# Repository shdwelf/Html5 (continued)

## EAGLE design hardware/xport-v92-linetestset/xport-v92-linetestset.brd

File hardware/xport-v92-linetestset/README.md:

# Isolated Line Test Set — `xport-v92-linetestset`

A lineman's test handset on a board. Test leads on one side, an earpiece and an
electret microphone on the other, with a 600:600 Ω wet isolation transformer in
between and a switch that chooses whether you are *part of* the call or merely
listening to it.

This is the legitimate member of the phreaking "box" family — the **beige box**,
which is not a fraud device at all but a standard telecom maintenance tool that
Fluke and Greenlee sell commercially. Clipping it onto a line that is not yours
is wiretapping and is illegal; the hardware is not. See
[`docs/phreaking-boxes-vlsi-notes.md`](../../docs/phreaking-boxes-vlsi-notes.md)
for the rest of that family and why this one is different.

Generated from
[`tools/xport-v92-linetestset-model.mjs`](../../tools/xport-v92-linetestset-model.mjs)
and verified by that tool's `--check`:

```
geometry: 69 pads, 33 placed elements, 27 nets
worst mains↔SELV creepage: 3.28 mm (T1.1 ↔ T1.6), limit 3 mm
schematic: 29 instances on a 520 × 420 mm sheet
OK — XML well-formed, every reference resolves, connectivity matches the model, geometry clean.
```

## Signal chain

```
test leads
  └─ F1 100mA ─ R1/R2 100R ─┬─ RV1 275V ─┬─ C1 100nF ─┐
                            └────────────┴────────────┴─ BR1 bridge rectifier
                                                            └─ K1 hook relay
                                                                 └─ T1 wet 600:600
                                                                      └─ hybrid
                                                                          ├─ TALK 600R ──► earpiece + electret
                                                                          └─ MON  10k ──► volume ──► earpiece
```

## The three things that make it a test set and not an audio tap

**1. The bridge rectifier.** A test set gets clipped onto pairs whose polarity
nobody knows. Full-wave rectifying ahead of everything else means the rest of
the circuit always sees the same orientation. Without `BR1`, half of every job
is guessing which lead is tip.

**2. TALK versus MONITOR are opposite requirements.** TALK goes off-hook and
terminates the line in 600 Ω so you can join the conversation. MONITOR bridges
at 10 kΩ, which is high enough not to load the line or disturb a call already in
progress, so you can listen and measure without anyone knowing. `SW1` selects
between them; there is no setting that does both.

**3. It runs from the line.** The electret bias (`R7` 2.2 k) and the line-present
LED (`R8` 1 k) are fed from the rectified loop. No battery to be flat when you
are standing at a cabinet in the rain, and the LED glows on ring voltage too, so
it doubles as an EMF indicator.

## DC loop budget in TALK

This decides whether the exchange sees an off-hook at all.

| element | resistance |
| --- | --- |
| F1 fuse | ~0.2 Ω |
| R1 + R2 surge limiters | 200 Ω |
| BR1 bridge | a few Ω effective |
| K1 contact | ~0.1 Ω |
| T1 primary DC resistance | 40–150 Ω |
| **total** | **240–350 Ω** (limit 400 Ω) |

## Safety

The left of the board is line-referenced. 48 V DC sits on the pair, ring peaks
above 150 V, and a lightning or power-cross event puts far more on it.

`T1` is the **only** isolation barrier between the line and the earpiece you put
against your head. It must be the **wet** type — specified to carry 20–50 mA of
DC loop current without saturating. A dry voice transformer of the same
impedance works on the bench and fails the moment the line goes off-hook.

Isolation resistance from the line side to any touchable metal has to hold
**5 MΩ measured at 100 V DC**. Measure it after assembly, before first use.

The 3 mm creepage is enforced by `tools/wallplug-drc.mjs` via
`BOARD.zones.mains` and `creepageMm: 3.0`, and `T1`'s primary pins are marked
line-referenced individually through `PARTS[].padZones`, so the checker measures
the transformer's own pin spacing rather than trusting its silk outline. As
built, the worst pair is **T1.1 ↔ T1.6 at 3.28 mm**.

## Files

| file | what |
| --- | --- |
| `xport-v92-linetestset.lbr` | 18 packages, 18 symbols, 19 devicesets |
| `xport-v92-linetestset.sch` | 29 instances on a 520 × 420 sheet |
| `xport-v92-linetestset.brd` | 69 pads, 33 elements, 27 nets, 110 × 80 mm |
| `BOM.md` | generated bill of materials |

Rebuild with `npm run build:xport-v92-linetestset`, or check without writing:
`node tools/build-wallplug-eagle.mjs --check --design xport-v92-linetestset`.

Fourteen of the packages are shared with
[`../xport-v92-audiobridge/`](../xport-v92-audiobridge/) by direct import rather
than by copy, so the two boards cannot drift apart on a footprint. Only the
bridge rectifier, SPDT toggle, earpiece and electret are new.

## What is not done

- **No routing.** The emitter places parts and verifies clearance; it does not
  route copper. `POUR` and the barrier keep-out are declared, traces are not.
- **Not measured.** No prototype. Return loss against the 10 dB requirement,
  frequency response, sidetone null and THD are all unmeasured, and the hybrid
  balance in particular has to be trimmed against a real line.
- **No sidetone or ringer.** A production butt set has both. This has an
  earpiece, a microphone and a volume control, and nothing else.
- **`LS1` and `MIC1` values are placeholders.** A 150 Ω earpiece and a generic
  electret are assumed; the bias resistor `R7`/`R10` divider was sized for a
  typical 2 V, 0.5 mA capsule, not for a specific part.
- **Hook drive is external.** `J2` expects a control signal; the set does not
  decide for itself when to go off-hook.

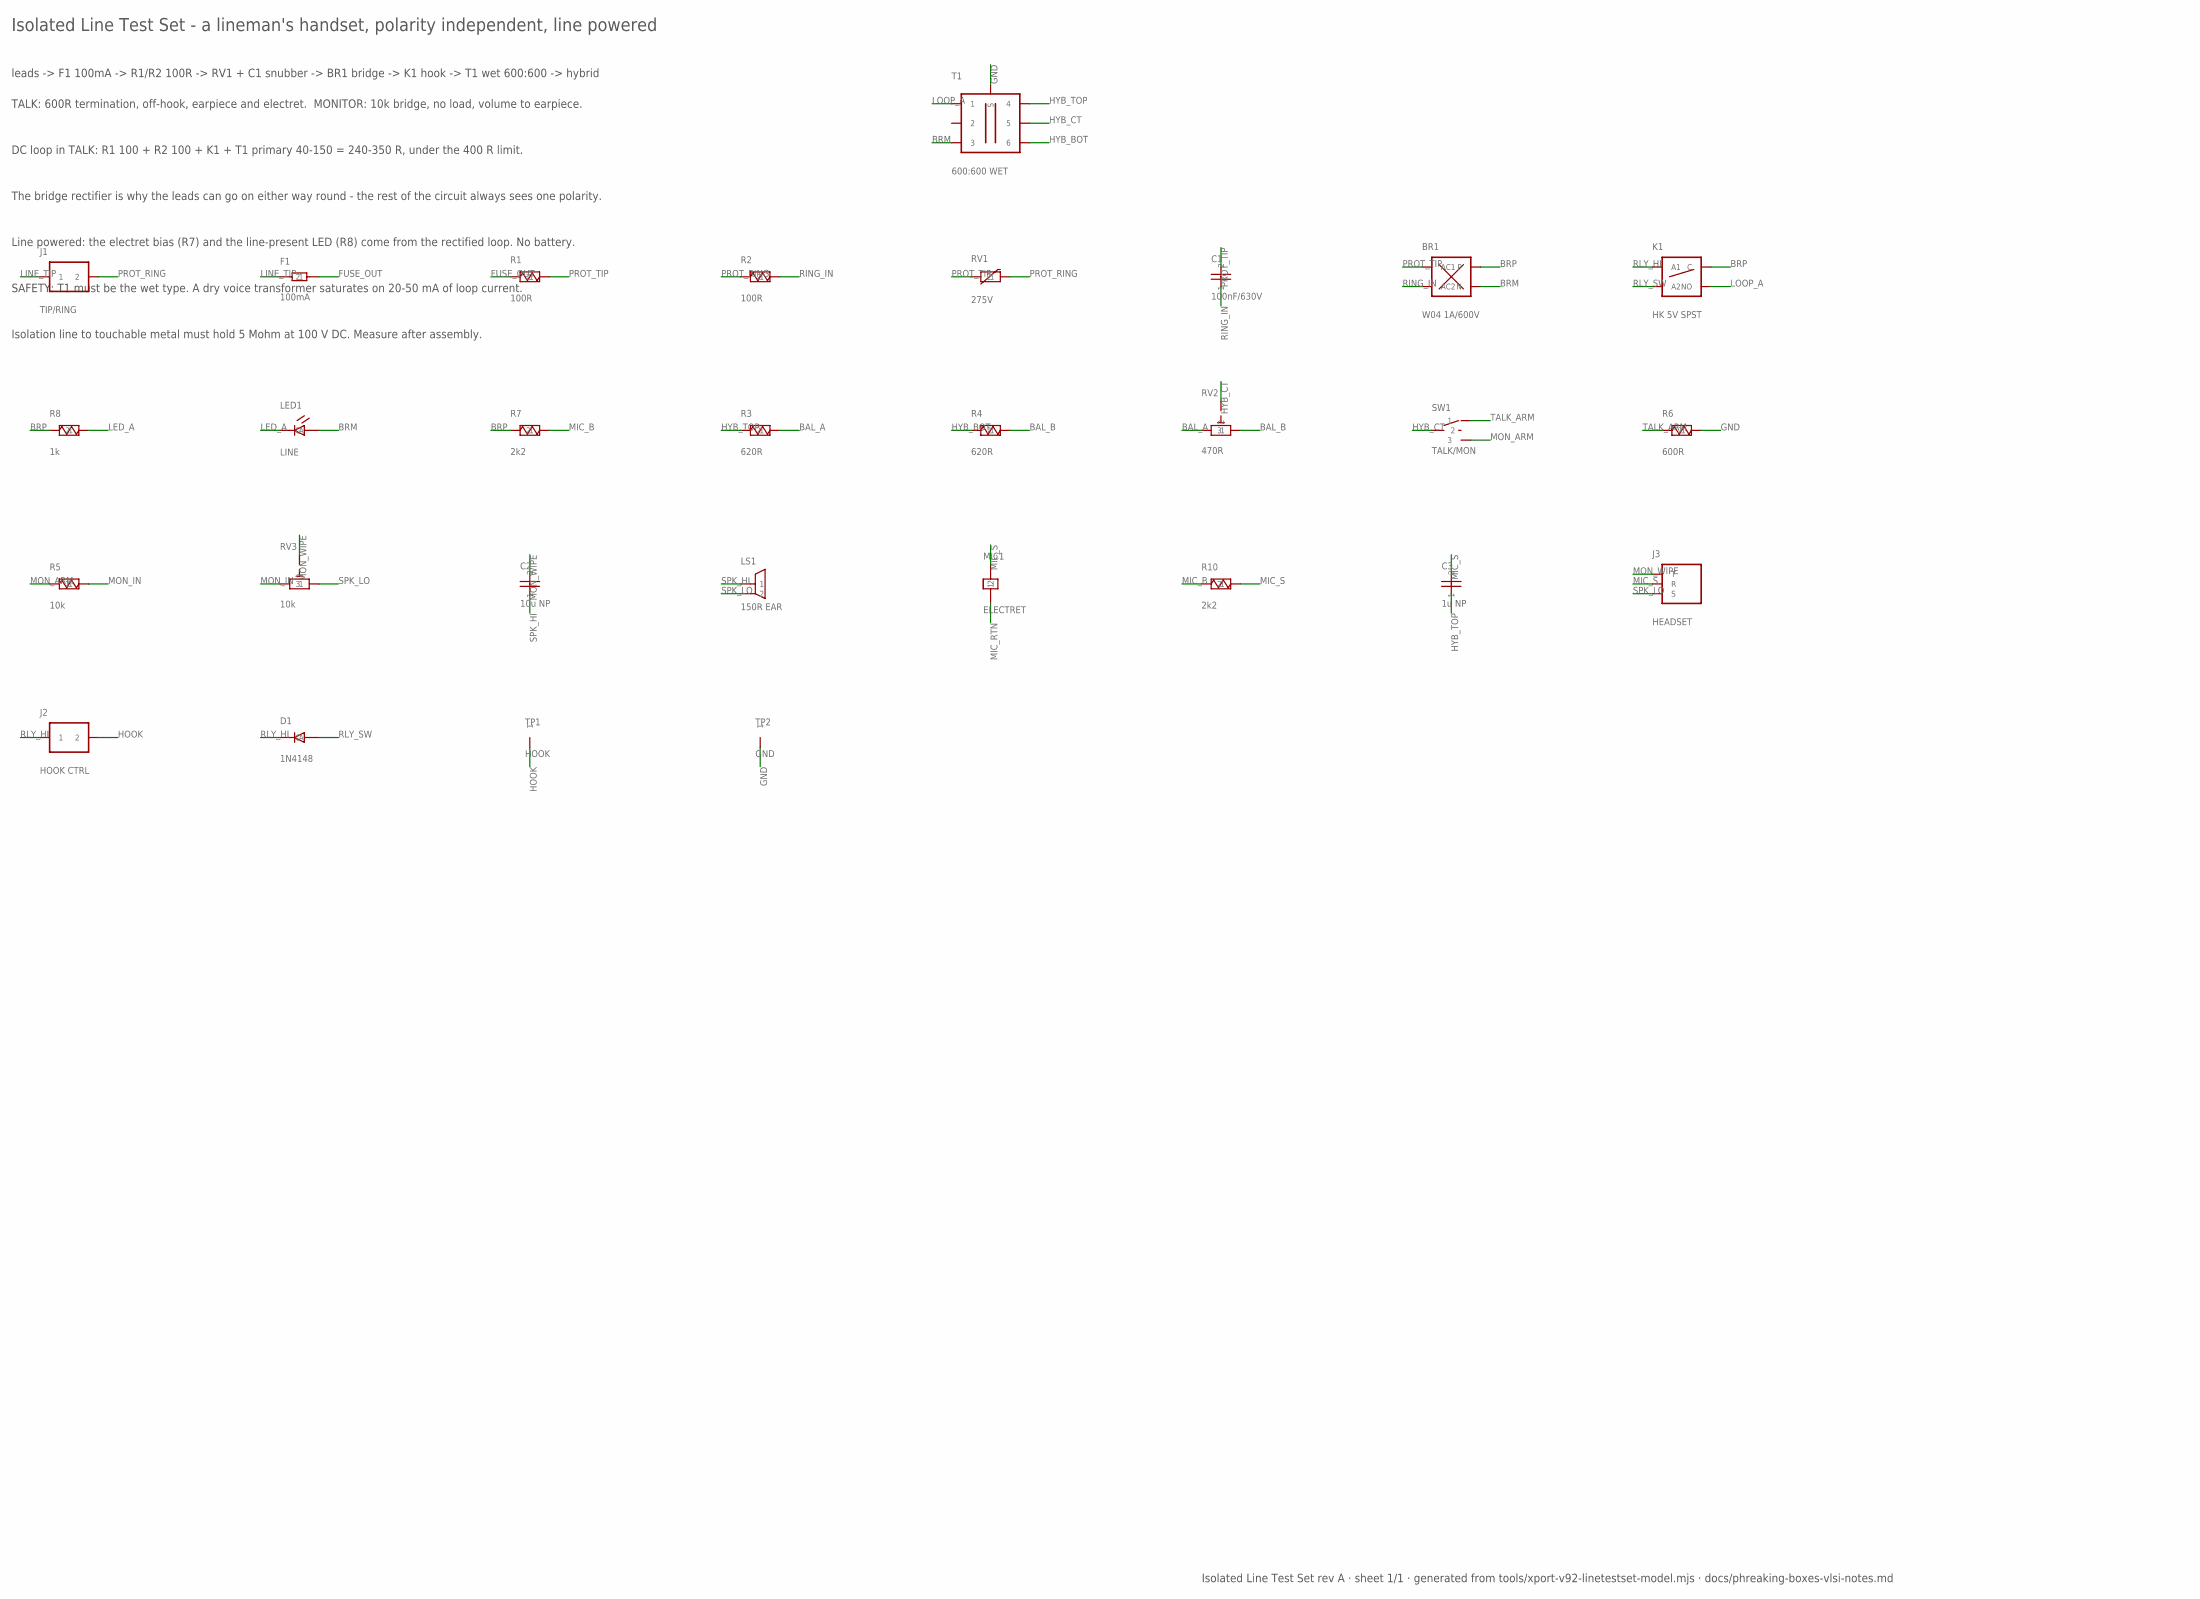
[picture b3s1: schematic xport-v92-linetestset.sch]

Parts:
BR1: W04 1A/600V; BRIDGE-WOB
C1: 100nF/630V; C-5.08
C2: 10u NP; C-5.08
C3: 1u NP; C-5.08
D1: 1N4148; DO41
F1: 100mA; R-7.62
J1: TIP/RING; TERM2-5.08
J2: HOOK CTRL; TERM2-5.08
J3: HEADSET; JACK-3P5
K1: HK 5V SPST; RELAY-SPST
LED1: LINE; LED-5MM
LS1: 150R EAR; SPEAKER-12
MIC1: ELECTRET; ELECTRET-10
R1, R2: 100R; R-7.62
R3, R4: 620R; R-7.62
R5: 10k; R-7.62
R6: 600R; R-7.62
R7, R10: 2k2; R-7.62
R8: 1k; R-7.62
RV1: 275V; MOV-7.62
RV2: 470R; TRIM-3P
RV3: 10k; TRIM-3P
SW1: TALK/MON; TOGGLE-SPDT
T1: 600:600 WET; XFMR-600
TP1: HOOK; TP
TP2: GND; TP

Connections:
BAL_A: R3.2, RV2.1
BAL_B: R4.2, RV2.3
BRM: BR1.- (N), LED1.2 (C), T1.3
BRP: BR1.+, K1.3 (C), R7.1, R8.1
FUSE_OUT: F1.2, R1.1
GND: R6.2, T1.S, TP2.1
HOOK: J2.2, TP1.1
HYB_BOT: R4.1, T1.6
HYB_CT: RV2.2, SW1.2, T1.5
HYB_TOP: C3.2, R3.1, T1.4
LED_A: LED1.1 (A), R8.2
LINE_TIP: F1.1, J1.1
LOOP_A: K1.4 (NO), T1.1
MIC_B: R7.2, R10.1
MIC_RTN: MIC1.2
MIC_S: C3.1, J3.2 (R), MIC1.1, R10.2
MON_ARM: R5.1, SW1.3
MON_IN: R5.2, RV3.1
MON_WIPE: C2.1, J3.1 (T), RV3.2
PROT_RING: J1.2, R2.1, RV1.2
PROT_TIP: BR1.~1 (AC1), C1.1, R1.2, RV1.1
RING_IN: BR1.~2 (AC2), C1.2, R2.2
RLY_HI: D1.1 (A), J2.1, K1.1 (A1)
RLY_SW: D1.2 (C), K1.2 (A2)
SPK_HI: C2.2, LS1.1
SPK_LO: J3.3 (S), LS1.2, RV3.3
TALK_ARM: R6.1, SW1.1

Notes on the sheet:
Isolated Line Test Set - a lineman's handset, polarity independent, line powered
leads -> F1 100mA -> R1/R2 100R -> RV1 + C1 snubber -> BR1 bridge -> K1 hook -> T1 wet 600:600 -> hybrid
TALK: 600R termination, off-hook, earpiece and electret. MONITOR: 10k bridge, no load, volume to earpiece.
DC loop in TALK: R1 100 + R2 100 + K1 + T1 primary 40-150 = 240-350 R, under the 400 R limit.
The bridge rectifier is why the leads can go on either way round - the rest of the circuit always sees one polarity.
Line powered: the electret bias (R7) and the line-present LED (R8) come from the rectified loop. No battery.
SAFETY: T1 must be the wet type. A dry voice transformer saturates on 20-50 mA of loop current.
Isolation line to touchable metal must hold 5 Mohm at 100 V DC. Measure after assembly.
Isolated Line Test Set rev A · sheet 1/1 · generated from tools/xport-v92-linetestset-model.mjs · docs/phreaking-boxes-vlsi-notes.md

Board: 2 copper layers, 33 parts (0 on the bottom side), 26 nets, no tracks yet.

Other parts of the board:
H1, H2, H3, H4: MOUNT-M3

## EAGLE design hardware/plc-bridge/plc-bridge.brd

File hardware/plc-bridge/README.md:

# Powerline Bridge — HomePlug Green PHY ↔ 10/100 Ethernet

Generated CAD. Do not edit these files: they are emitted by
`tools/build-wallplug-eagle.mjs --design=plc-bridge` from
`tools/plc-bridge-model.mjs`, and `--check` re-derives them and compares.

| file | what it is |
| --- | --- |
| `plc-bridge.lbr` | 22 packages, 18 symbols, 21 devicesets |
| `plc-bridge.sch` | 1 sheet, 41 instances, 33 nets |
| `plc-bridge.brd` | 160 × 100 mm, 2 layers, 45 elements, 171 pads — **unrouted on purpose** |
| `BOM.md` | every reference, its package, fit/DNP, zone and note |

## What it does

A wallplug that puts Ethernet frames on the building's power wiring and hands them
to a wired 10/100 port:

```
L ── F1 ──┬──────────── PS1 (IRM-05-5, isolated 5 V) ── FB1 ── U1 (LM2576S-3.3) ── 3V3
          │                                                        │
N ────────┼────────────────────────────────────────────────────────┤
          └── U2 pins 16/17 (L) and 15 (N)      U2 = PLC Stamp mini 2 (QCA7005)
                                                  │ SPI slave, mode 3, ≤ 12 MHz
                                                  U3 = ESP32-WROOM-32E, SPI master
                                                  │ VSPI
                                                  U4 = WIZnet WIZ850io → RJ45
```

Green PHY is 10 Mbit/s. It is the ISO 15118 / EV-charging profile and the
smart-grid profile of HomePlug, and it coexists with HomePlug AV/AV2 on the same
wiring. It does **not** interoperate with ITU-T G.hn (turbo coding vs LDPC), so a
G.hn adapter on the same phase degrades both.

## Design rules

| rule | value | where it comes from |
| --- | --- | --- |
| mains ↔ SELV creepage | **8.0 mm** | PLC Stamp mini 2 datasheet rev 13 §8.3: "Isolation between L/N terminals and all other connections: 8 mm creepage / 6.5 mm clearance" |
| mains ↔ SELV clearance | 6.5 mm | same |
| isolation test voltage | 4000 Vac | same (the module provides it; the board must not undo it) |
| minimum pad-to-pad | 0.35 mm | `--check` geometry rule |
| mounting hole ↔ copper | 3.2 mm | `--check` |
| board | 160 × 100 mm, 2 layers, 1.6 mm FR-4 | |

`--check` reports the worst mains↔SELV pair. On this board it is **U2.15 ↔ U2.13 =
13.12 mm** — the modem's own N pad against its own ZC_IN pad, i.e. the vendor's
footprint honouring its own §8.3 claim. `tests/23-variants.mjs` asserts that.

## Power budget (datasheet maxima, not typicals)

| rail | source | loads | margin |
| --- | --- | --- | --- |
| 5 V | IRM-05-5, 5 W / 1 A | U1 buck input ≈ 600 mA | 40 % |
| 3.3 V | LM2576S-3.3, 3 A | U2 300 mA (§8.2 IDD max) + U3 200 mA (radio **off**) + U4 180 mA + LEDs 20 mA = 700 mA | 77 % |

The ESP32's Wi-Fi radio is not needed on a board that has an Ethernet port; if you
enable it anyway, add ≈300 mA of TX burst to the 3.3 V rail and re-check.

## The modem, and the variant trap

Fit **I2PLCBMN-ISC-004-T** (or `-R` for tape and reel): QCA7005, industrial
−40…85 °C, SPI, **CE Class B**, PLC transformer I2PLCTR-1 (1:4:5) and zero-cross
detection **on the module**, pin 13 left floating (§12.1).

The automotive variants (`…-ISE-…` EVSE, `…-ISP-…` PEV) have a 1:1:1 transformer,
no zero-cross detector, and the datasheet says it in terms that cannot be
misread: *"Automotive variants of PLC Stamp mini 2 are not designed to work on
mains."* They tie pins 16/17 to GND and couple through pin 15 only.

That is exactly what the published PIONIX EVerest "Yak" carrier does — it fits the
automotive variant and couples to an EV control pilot through two 2.7 nF / 2 kV
1210 capacitors in series, a GBLC03C TVS and a YT-35636 transformer
(`Yak/everestCM4.xml`, nets `/PLC Modem/CP`, `Net-(C28-Pad2)`, `Net-(C29-Pad2)`).
It is a real Green PHY design and it is **not** a mains coupling. Do not copy it
onto this board.

## Host wiring

| ESP32-WROOM-32E | PLC Stamp mini 2 | note |
| --- | --- | --- |
| IO14 | SERIAL_1 (CLK) | HSPI clock |
| IO12 | SERIAL_3 (MISO) | |
| IO13 | SERIAL_4 (MOSI) | |
| IO15 | SERIAL_2 (CS) | 10 kΩ pull-down R10: IO15 is a strapping pin (MTDO) |
| IO4 | SERIAL_0 (INT) | |
| IO32 | RESET_L | also TP5 |
| IO18/19/23/5 | — | VSPI to the WIZ850io (SCLK/MISO/MOSI/CS) |
| IO33 / IO26 | — | WIZ850io !INT / !RST (R9 10 kΩ pull-up) |
| TXD0 / RXD0 | — | J2 programming header |

SPI is Motorola **mode 3** (CPOL=1, CPHA=1), CS held low for the whole message
(burst), clock period ≥ 83.3 ns → **12 MHz maximum** (datasheet §10.2.2). Software
precedent: `github.com/qca/open-plc-utils` (plctool, slac) and
`github.com/uhi22/wt32eth01-ethernet-to-qca7000-bridge`.

## Bootstrap parts (datasheet figures 3 and 4)

| ref | value | why |
| --- | --- | --- |
| R5, R6 | 3.3 kΩ | GPIO_0 / GPIO_1 LED bootstrap; after boot GPIO_0 = PLC link, GPIO_1 = Simple Connect blink at 1 Hz |
| R4 | 10 kΩ | GPIO_3 pull-up |
| R3 | 100 Ω | GPIO_3 series |
| C5 | 100 pF | across SW3, debounce |
| SW3 | tact | 0.5–3 s Simple Connect, 5–8 s randomise NMK, 10–15 s factory defaults (table 5) |
| R2 | 10 kΩ **DNP** | ZC_IN pull-down — only for DC-line coupling (§8.2 note 2) |

GPIO_0/1/2 are boot straps (table 4): GPIO_0 boot source, GPIO_1 host interface
(the module preloads a 10 kΩ pull-down = SPI slave), GPIO_2 SPI burst/legacy.
GPIO_2 is unused after boot and is listed in `UNCONNECTED`.

## Bring-up

1. Power up with **no** card/host: check 5 V at TP1, 3.3 V at TP4. The LM2576's
   ON/OFF pin is tied to GND (always on) and its FB pin is internally bonded on
   the fixed-output part, so both are left as fitted.
2. Press and hold SW3 for 0.5–3 s, then watch LED3: a 1 Hz blink means the module
   is in Simple Connect mode. LED2 (GPIO_0) lights when the network is joined.
3. Flash the ESP32 over J2 (UART0, 115200 8N1): hold SW2 (IO0) while pressing SW1
   (EN) to enter the download bootloader.
4. From the host, drive the modem with open-plc-utils: `plctool -i <if> …`, then
   `slac` to join, then bridge frames between the QCA7000 SPI interface and the
   W5500's socket buffers.

## Safety

* U2 pads 15/16/17 are at mains potential. The module's isolation is 4000 Vac with
  8 mm creepage / 6.5 mm clearance; the board keeps 8.0 mm, and the silkscreen
  draws the keep-out around those three pads.
* PS1 (MEAN WELL IRM-05-5) is a certified encapsulated supply — EN60950-1 /
  UL60950-1, CB, CE, cURus, TUV. Its isolation is inside the module.
* F1 is in the line conductor only; MOV1 is after the fuse. PE lands on J1.3 and
  TP3 and is **never** bonded to SELV ground on this PCB.
* The module is MSL 3 and tolerates at most two reflows (§13, IPC/JEDEC J-STD-020
  and J-STD-033).
* Not certified. A mains-coupled PLC product needs IEC/EN 62368-1 assessment plus
  the coupling and emissions work; the module's CE Class B variant is the starting
  point, not the finish.

## Footprint provenance

| package | source |
| --- | --- |
| `PLCSTAMP` | `github.com/PionixPublic/reference-hardware` → `Yak/lib/ev-devboard.pretty/PLC_Stamp_mini_2.kicad_mod`; outline and the missing pad 14 per chargebyte datasheet §11 |
| `ESP32WROOM` | KiCad official `RF_Module/ESP32-WROOM-32` |
| `WIZ850IO` | `github.com/es-ude/kicad-library` → `custom_library.pretty/WIZ850IO.kicad_mod`; outline 23 × 25.75 mm from the WIZnet datasheet |
| `IRM055` | `github.com/sebdehne/DehneEVSE-Hardware` → `CONV_IRM-05-5.kicad_mod` (pad names AC/L, AC/N, VNEG, VPOS renumbered 1–4) |
| `LM2576S`, `LRAD12`, `CUI_TB003`, `R0603`, `C0603` | KiCad official library / PIONIX library |
| `DO41` | hand-drawn in `tools/eda-blocks.mjs`, 7.62 mm axial |

`tools/import-kicad-footprints.mjs` re-fetches all of them and records repo, path
and fetch date in `tools/eda-packages.mjs`.

## Not done

* No routing. The board is placed and rule-checked; the traces, the ground pour
  stitching and the RF/analogue separation are left to whoever builds it.
* The chip-level alternative (bare QCA7000 in QFN-68 with 270 nH / 1.5 nF / 120 Ω
  AFE parts, 25 MHz crystal, 25Q16 flash) is documented in
  `tools/replacement-parts.mjs` with its footprint imported, but not laid out: the
  published hobby board that supplies those values is marked "TODO Not tested" by
  its author, and the module route buys a 4000 Vac isolation spec instead.
* The external zero-cross circuit of datasheet figure 6 (2200 pF, 820 kΩ,
  CGRM4007-G, TCLT1000 optocoupler, 100 Ω, 39 kΩ, 220 nF, 1000 pF, 1 µF) is
  recorded in `tools/replacement-parts.mjs` but not placed: only automotive
  variants need it.

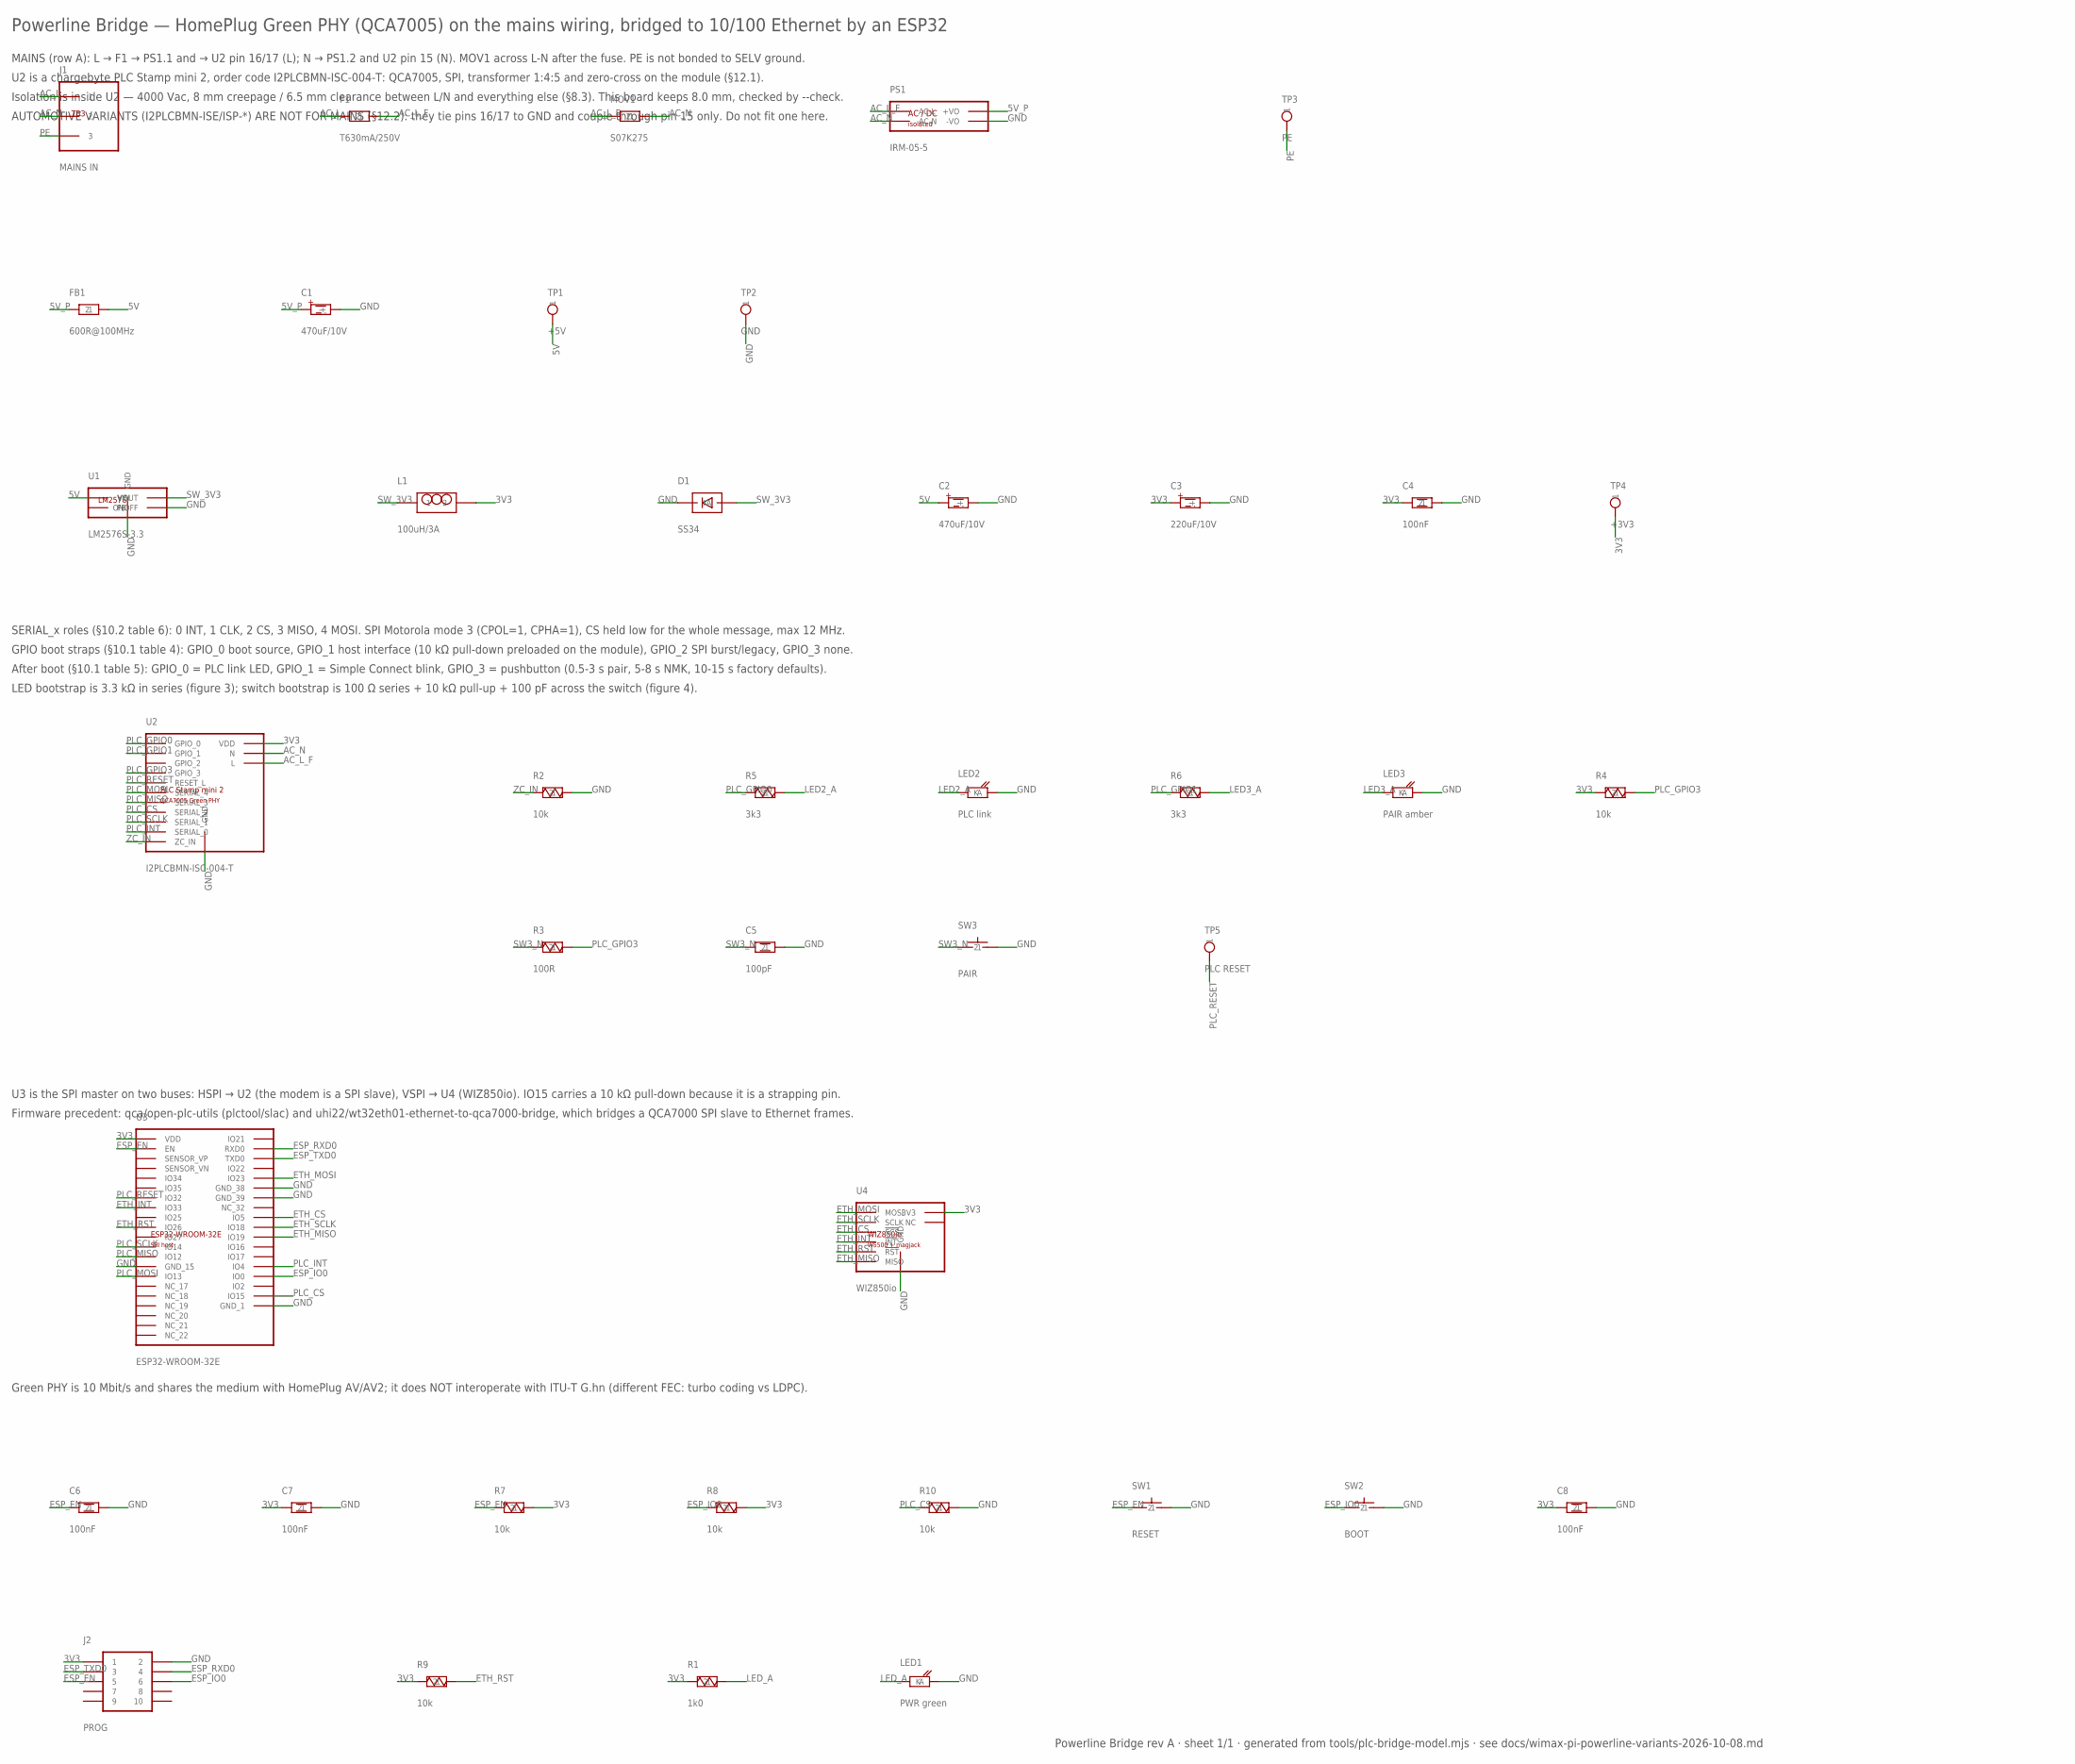
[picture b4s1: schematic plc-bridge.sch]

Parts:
C1, C2: 470uF/10V; CP-D10-P5
C3: 220uF/10V; CP-D10-P5
C4, C6, C7, C8: 100nF; C0603
C5: 100pF; C-5.08
D1: SS34; DO41
F1: T630mA/250V; FUSE-RADIAL
FB1: 600R@100MHz; FB-7.62
J1: MAINS IN; CUI_TB003
J2: PROG; HDR-2X5
L1: 100uH/3A; LRAD12
LED1: PWR green; LED-5MM
LED2: PLC link; LED-5MM
LED3: PAIR amber; LED-5MM
MOV1: S07K275; MOV07
PS1: IRM-05-5; IRM055
R1: 1k0; R-7.62
R2, R4, R7, R8, R9, R10: 10k; R-7.62
R3: 100R; R-7.62
R5, R6: 3k3; R-7.62
SW1: RESET; SW-TACT-6MM
SW2: BOOT; SW-TACT-6MM
SW3: PAIR; SW-TACT-6MM
TP1: +5V; TP
TP2: GND; TP
TP3: PE; TP
TP4: +3V3; TP
TP5: PLC RESET; TP
U1: LM2576S-3.3; LM2576S
U2: I2PLCBMN-ISC-004-T; PLCSTAMP
U3: ESP32-WROOM-32E; ESP32WROOM
U4: WIZ850io; WIZ850IO

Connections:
3V3: C3.+, C4.1, C7.1, C8.1, J2.1, L1.2, R1.1, R4.1, R7.2, R8.2, R9.1, TP4.1, U2.12 (VDD), U3.2 (VDD), U4.8 (3V3), U4.9 (3V3)
5V: C2.+, FB1.2, TP1.1, U1.1 (VIN)
5V_P: C1.+, FB1.1, PS1.4 (+VO)
AC_L: F1.1, J1.1
AC_L_F: F1.2, MOV1.1, PS1.1 (AC-L), U2.16 (L), U2.17 (L)
AC_N: J1.2, MOV1.2, PS1.2 (AC-N), U2.15 (N)
ESP_EN: C6.1, J2.5, R7.1, SW1.1, U3.3 (EN)
ESP_IO0: J2.6, R8.1, SW2.1, U3.25 (IO0)
ESP_RXD0: J2.4, U3.34 (RXD0)
ESP_TXD0: J2.3, U3.35 (TXD0)
ETH_CS: U3.29 (IO5), U4.5 (!SCS)
ETH_INT: U3.9 (IO33), U4.6 (!INT)
ETH_MISO: U3.31 (IO19), U4.12 (MISO)
ETH_MOSI: U3.37 (IO23), U4.3 (MOSI)
ETH_RST: R9.2, U3.11 (IO26), U4.11 (!RST)
ETH_SCLK: U3.30 (IO18), U4.4 (SCLK)
GND: C1.-, C2.-, C3.-, C4.2, C5.2, C6.2, C7.2, C8.2, D1.A, J2.2, LED1.2 (K), LED2.2 (K), LED3.2 (K), PS1.3 (-VO), R2.2, R10.2, SW1.2, SW2.2, SW3.2, TP2.1, U1.3 (GND), U1.3_2 (GND), U1.5 (ONOFF), U1.P7 (GND), U1.P8 (GND), U1.P9 (GND), U1.P10 (GND), U2.11 (GND), U2.18 (GND), U2.19 (GND), U2.20 (GND), U2.21 (GND), U2.22 (GND), U2.23 (GND), U2.24 (GND), U2.25 (GND), U3.1 (GND_1), U3.15 (GND_15), U3.38 (GND_38), U3.39 (GND_39), U4.1 (GND), U4.2 (GND), U4.7 (GND)
LED2_A: LED2.1 (A), R5.2
LED3_A: LED3.1 (A), R6.2
LED_A: LED1.1 (A), R1.2
PE: J1.3, TP3.1
PLC_CS: R10.1, U2.8 (SERIAL_2), U3.23 (IO15)
PLC_GPIO0: R5.1, U2.1 (GPIO_0)
PLC_GPIO1: R6.1, U2.2 (GPIO_1)
PLC_GPIO3: R3.2, R4.2, U2.4 (GPIO_3)
PLC_INT: U2.10 (SERIAL_0), U3.26 (IO4)
PLC_MISO: U2.7 (SERIAL_3), U3.14 (IO12)
PLC_MOSI: U2.6 (SERIAL_4), U3.16 (IO13)
PLC_RESET: TP5.1, U2.5 (RESET_L), U3.8 (IO32)
PLC_SCLK: U2.9 (SERIAL_1), U3.13 (IO14)
SW3_N: C5.1, R3.1, SW3.1
SW_3V3: D1.K, L1.1, U1.2 (VOUT)
ZC_IN: R2.1, U2.13 (ZC_IN)

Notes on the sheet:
Powerline Bridge — HomePlug Green PHY (QCA7005) on the mains wiring, bridged to 10/100 Ethernet by an ESP32
MAINS (row A): L → F1 → PS1.1 and → U2 pin 16/17 (L); N → PS1.2 and U2 pin 15 (N). MOV1 across L-N after the fuse. PE is not bonded to SELV ground.
U2 is a chargebyte PLC Stamp mini 2, order code I2PLCBMN-ISC-004-T: QCA7005, SPI, transformer 1:4:5 and zero-cross on the module (§12.1).
Isolation is inside U2 — 4000 Vac, 8 mm creepage / 6.5 mm clearance between L/N and everything else (§8.3). This board keeps 8.0 mm, checked by --check.
AUTOMOTIVE VARIANTS (I2PLCBMN-ISE/ISP-*) ARE NOT FOR MAINS (§12.2): they tie pins 16/17 to GND and couple through pin 15 only. Do not fit one here.
SERIAL_x roles (§10.2 table 6): 0 INT, 1 CLK, 2 CS, 3 MISO, 4 MOSI. SPI Motorola mode 3 (CPOL=1, CPHA=1), CS held low for the whole message, max 12 MHz.
GPIO boot straps (§10.1 table 4): GPIO_0 boot source, GPIO_1 host interface (10 kΩ pull-down preloaded on the module), GPIO_2 SPI burst/legacy, GPIO_3 none.
After boot (§10.1 table 5): GPIO_0 = PLC link LED, GPIO_1 = Simple Connect blink, GPIO_3 = pushbutton (0.5-3 s pair, 5-8 s NMK, 10-15 s factory defaults).
LED bootstrap is 3.3 kΩ in series (figure 3); switch bootstrap is 100 Ω series + 10 kΩ pull-up + 100 pF across the switch (figure 4).
U3 is the SPI master on two buses: HSPI → U2 (the modem is a SPI slave), VSPI → U4 (WIZ850io). IO15 carries a 10 kΩ pull-down because it is a strapping pin.
Firmware precedent: qca/open-plc-utils (plctool/slac) and uhi22/wt32eth01-ethernet-to-qca7000-bridge, which bridges a QCA7000 SPI slave to Ethernet frames.
Green PHY is 10 Mbit/s and shares the medium with HomePlug AV/AV2; it does NOT interoperate with ITU-T G.hn (different FEC: turbo coding vs LDPC).
Powerline Bridge rev A · sheet 1/1 · generated from tools/plc-bridge-model.mjs · see docs/wimax-pi-powerline-variants-2026-10-08.md

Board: 2 copper layers, 45 parts (0 on the bottom side), 33 nets, no tracks yet.

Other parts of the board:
H1, H2, H3, H4: MOUNT-M3
